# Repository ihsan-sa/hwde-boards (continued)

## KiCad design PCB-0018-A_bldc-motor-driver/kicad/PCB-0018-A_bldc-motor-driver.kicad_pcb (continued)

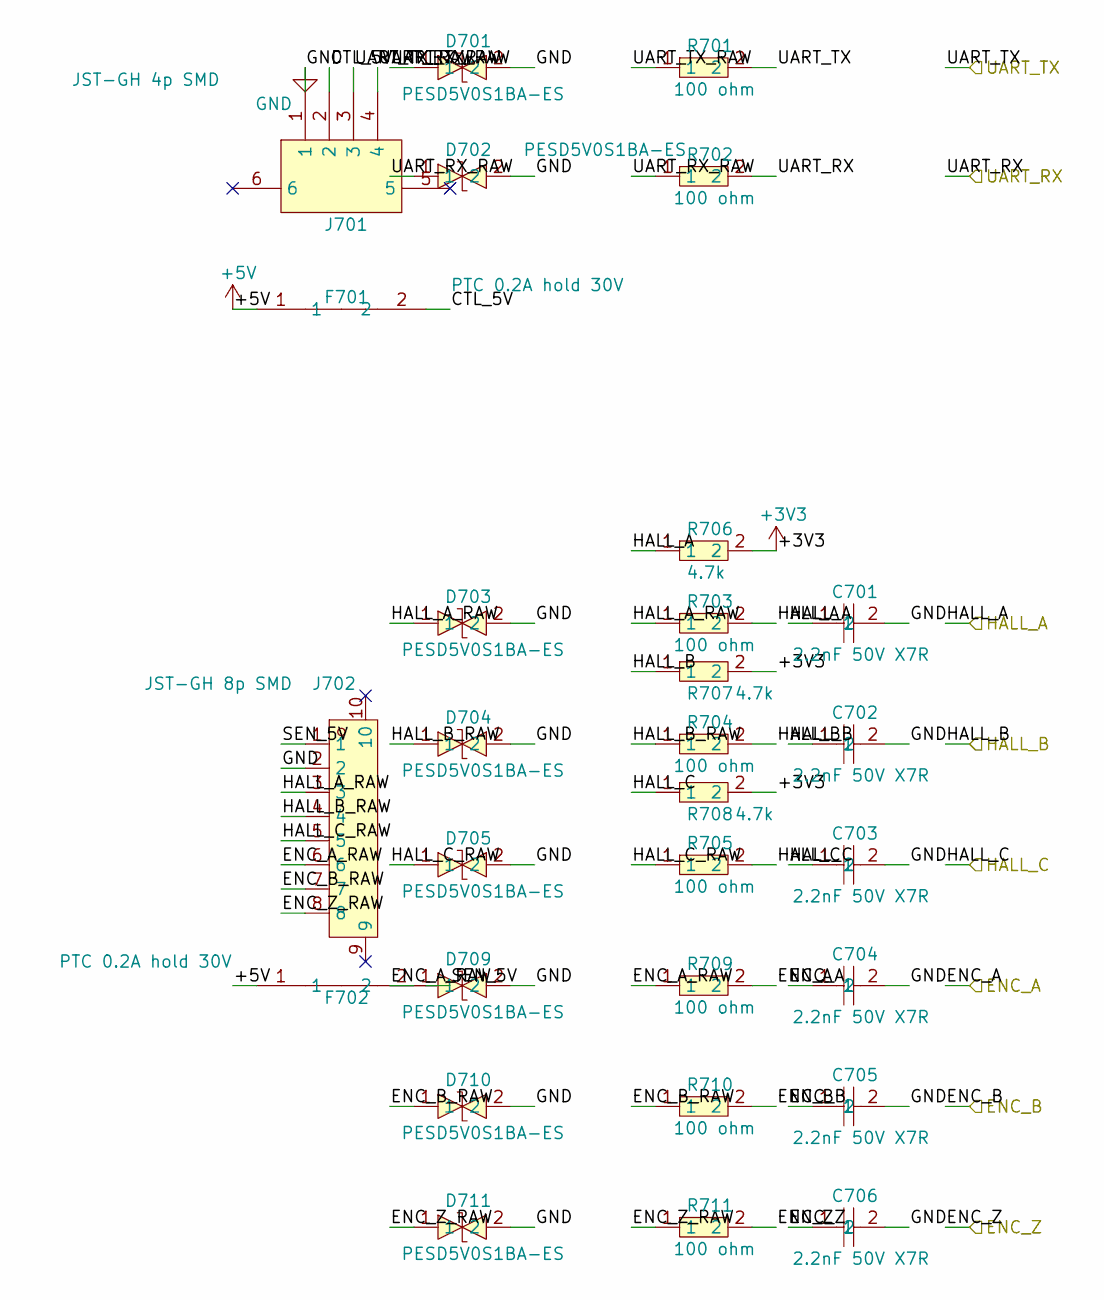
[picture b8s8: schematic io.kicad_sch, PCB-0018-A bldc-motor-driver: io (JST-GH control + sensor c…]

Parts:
C701, C702, C703, C704, C705, C706: 2.2nF 50V X7R; C0603; LCSC C1604
D701, D702, D703, D704, D705, D709, D710, D711: PESD5V0S1BA-ES; SOD-323_L1.7-W1.3-LS2.6-BI; LCSC C5180216
F701, F702: PTC 0.2A hold 30V; F1206; LCSC C69680
J701: JST-GH 4p SMD; CONN-SMD_4P-P1.25_SM04B-GHS-TB-LF-SN; LCSC C189895
J702: JST-GH 8p SMD; CONN-SMD_SH-SM08B-GHS-TB; LCSC C42376901
R701, R702, R703, R704, R705, R709, R710, R711: 100 ohm; R0603; LCSC C22775
R706, R707, R708: 4.7k; R0603; LCSC C23162

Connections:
+3V3: R706.2, R707.2, R708.2; also elsewhere on the board
+5V: F701.1, F702.1; also elsewhere on the board
/ENC_A: C704.1, R709.2; also elsewhere on the board
/ENC_B: C705.1, R710.2; also elsewhere on the board
/ENC_Z: C706.1, R711.2; also elsewhere on the board
/HALL_A: C701.1, R703.2, R706.1; also elsewhere on the board
/HALL_B: C702.1, R704.2, R707.1; also elsewhere on the board
/HALL_C: C703.1, R705.2, R708.1; also elsewhere on the board
/UART_RX: R702.2; also elsewhere on the board
/UART_TX: R701.2; also elsewhere on the board
/io/CTL_5V: F701.2, J701.2
/io/ENC_A_RAW: D709.1, J702.6, R709.1
/io/ENC_B_RAW: D710.1, J702.7, R710.1
/io/ENC_Z_RAW: D711.1, J702.8, R711.1
/io/HALL_A_RAW: D703.1, J702.3, R703.1
/io/HALL_B_RAW: D704.1, J702.4, R704.1
/io/HALL_C_RAW: D705.1, J702.5, R705.1
/io/SEN_5V: F702.2, J702.1
/io/UART_RX_RAW: D702.1, J701.4, R702.1
/io/UART_TX_RAW: D701.1, J701.3, R701.1
GND: C701.2, C702.2, C703.2, C704.2, C705.2, C706.2, D701.2, D702.2, D703.2, D704.2, D705.2, D709.2, D710.2, D711.2, J701.1, J702.2; also elsewhere on the board

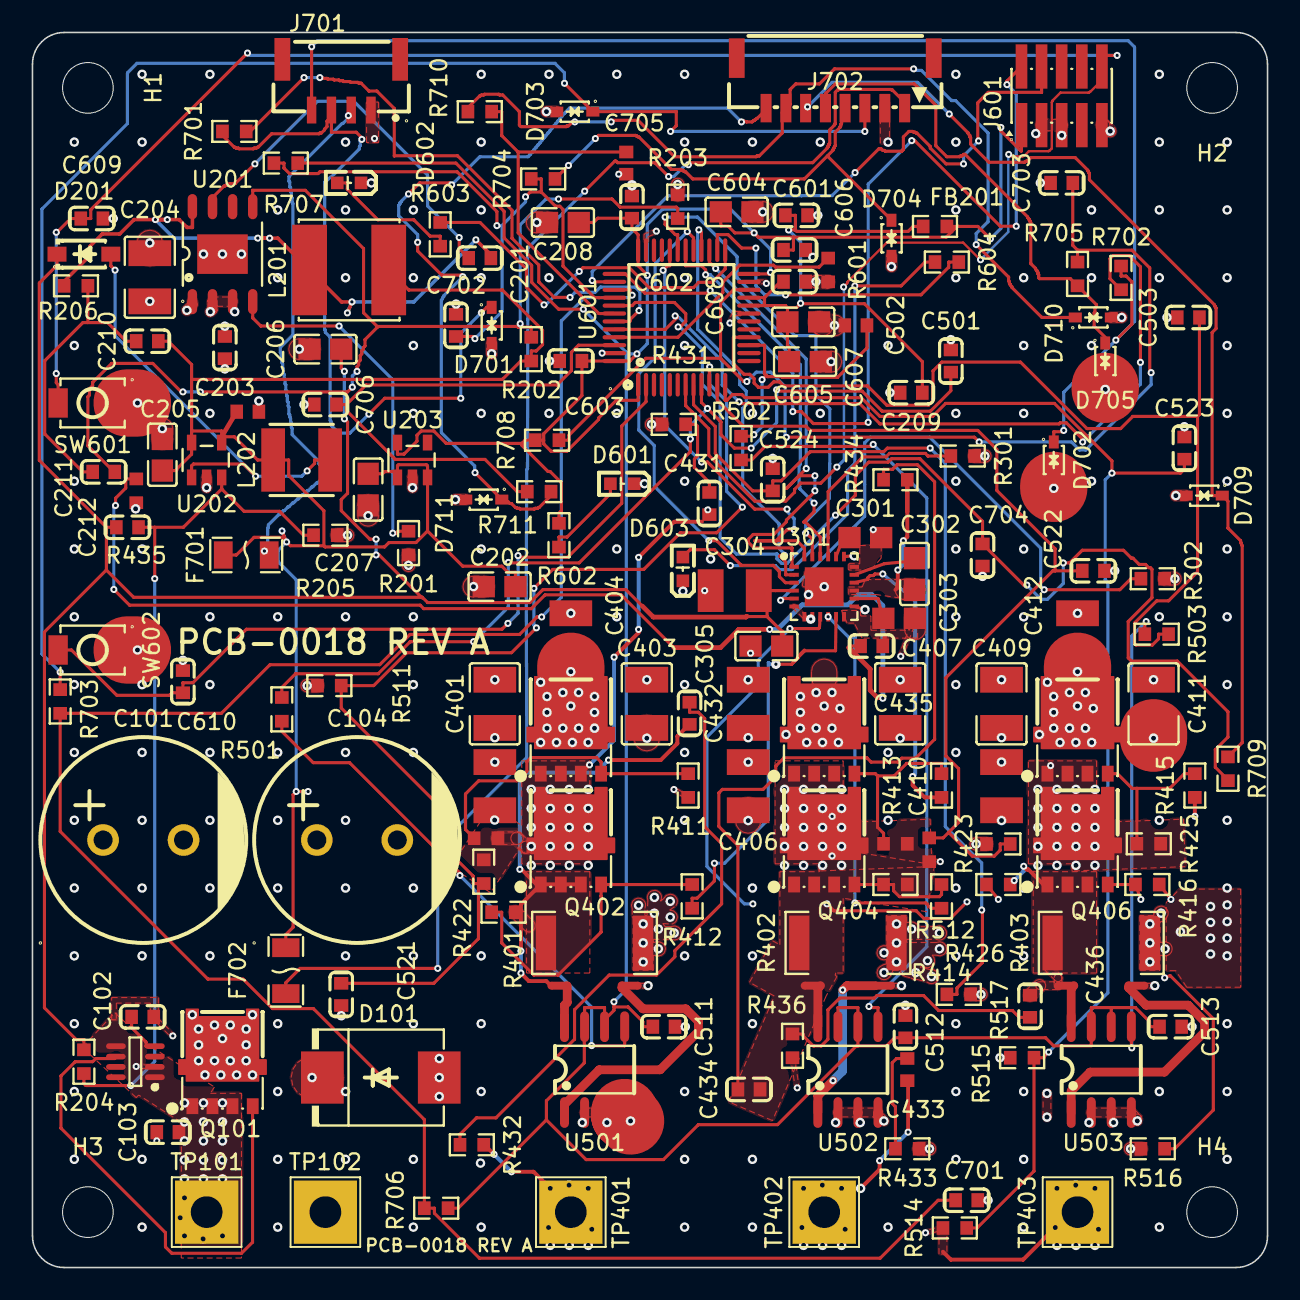
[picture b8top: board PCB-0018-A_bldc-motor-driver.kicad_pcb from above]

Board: 4 copper layers, 78.0 x 78.0 mm, 175 parts (1 on the bottom side), 95 nets.

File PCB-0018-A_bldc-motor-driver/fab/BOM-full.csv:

Comment,Designator,Qty Per Board,Footprint,MPN,LCSC,Assembly Class,Instructions
470uF 63V,"C101,C104",2,CAP-TH_BD13.0-P5.00-D1.2-FD,,C106675,smt_placed,
100nF 50V X7R,"C102,C103,C203,C209,C211,C213,C511,C512,C513,C524,C601,C602,C603,C608,C609,C610",16,C0603,,C14663,smt_placed,
2.2nF 50V X7R,"C201,C210,C501,C502,C503,C521,C522,C523,C701,C702,C703,C704,C705,C706",14,C0603,,C1604,smt_placed,
22uF 25V X5R,C202,1,C0805,,C45783,smt_placed,
10uF 50V X7R,"C204,C304,C401,C402,C403,C405,C406,C407,C409,C410,C411",11,C1210,,C2918502,smt_placed,
10uF 25V X5R,C205,1,C0805,,C15850,smt_placed,
1uF 50V X7R,"C206,C207,C208,C301,C302,C303,C305,C605,C607",9,C0805,,C28323,smt_placed,
1nF 50V X7R,C212,1,C0603,,C1588,smt_placed,
100nF 50V X7R,"C404,C408,C412",3,C1210,,C76567,smt_placed,
4.7uF 25V X5R,C604,1,C0805,,C1779,smt_placed,
10nF 50V X7R,C606,1,C0603,,C57112,smt_placed,
SMCJ28A,D101,1,SMC_L6.9-W5.8-LS7.9-RD,,C2943858,smt_placed,
MBR0520L,D201,1,SOD-123_L2.7-W1.6-LS3.7-RD-1,,C5563735,smt_placed,
LED green (power),D601,1,LED-SMD_L1.6-W0.8-R-RD,,C12624,smt_placed,
LED yellow (status),D602,1,LED-SMD_L1.6-W0.8-R-RD,,C2287,smt_placed,
LED red (fault),D603,1,LED-SMD_L1.6-W0.8-R-RD,,C2286,smt_placed,
PESD5V0S1BA-ES,"D701,D702,D703,D704,D705,D709,D710,D711",8,SOD-323_L1.7-W1.3-LS2.6-BI,,C5180216,smt_placed,
PTC 0.2A hold 30V,"F701,F702",2,F1206,,C69680,smt_placed,
600ohm@100MHz ferrite,FB201,1,R0603,,C1002,smt_placed,
SWD 2x5 1.27mm,J601,1,CONN-SMD_10P-P1.27_XFCN_PZ127VS-12-10-H10-A38,,C2935458,smt_placed,
JST-GH 4p SMD,J701,1,CONN-SMD_4P-P1.25_SM04B-GHS-TB-LF-SN,,C189895,smt_placed,
JST-GH 8p SMD,J702,1,CONN-SMD_SH-SM08B-GHS-TB,,C42376901,smt_placed,
22uH shielded,L201,1,IND-SMD_L6.0-W6.0,,C2849539,smt_placed,
22uH shielded,L202,1,IND-SMD_L4.0-W4.0_LQH44PN2R2MP0L,,C135264,smt_placed,
NTMFS5C628NL,"Q101,Q401,Q402,Q403,Q404,Q405,Q406",7,DFN-5_L4.9-W5.9-P1.27-LS6.2-BL,,C145537,smt_placed,
31.6k 1%,R201,1,R0603,,C25967,smt_placed,
33.2k 1%,R202,1,R0603,,C23003,smt_placed,
10k,"R203,R205,R302,R421,R422,R423,R424,R425,R426,R511,R513,R515,R517",13,R0603,,C25804,smt_placed,
86.6k 1%,R204,1,R0603,,C23121,smt_placed,
100k,R206,1,R0603,,C25803,smt_placed,
40.2k 1%,R301,1,R0603,,C12447,smt_placed,
3mR 2512 3W 1%,"R401,R402,R403",3,R2512,,C5375459,smt_placed,
10R,"R411,R412,R413,R414,R415,R416",6,R0603,,C22859,smt_placed,
100 ohm,"R501,R502,R503,R701,R702,R703,R704,R705,R709,R710,R711",11,R0603,,C22775,smt_placed,
150k,"R510,R512,R514,R516",4,R0603,,C22807,smt_placed,
10k 1%,R601,1,R0603,,C25804,smt_placed,
1k 1%,"R602,R603,R604",3,R0603,,C21190,smt_placed,
4.7k,"R706,R707,R708",3,R0603,,C23162,smt_placed,
Reset switch SMD,SW601,1,SW-SMD_L3.9-W3.0-P4.45,,C720477,smt_placed,
User switch SMD,SW602,1,SW-SMD_L3.9-W3.0-P4.45,,C720477,smt_placed,
LM74500-Q1,U101,1,SOT-23-8_L3.0-W1.7-P0.65-LS2.8-BR,,C5219210,smt_placed,
LM5164,U201,1,SO-8_L4.9-W3.9-P1.27-LS6.0-BL-EP,,C477928,smt_placed,
TPS61040,U202,1,SOT-23-5_L2.9-W1.6-P0.95-LS2.8-BL,,C7722,smt_placed,
TLV75733,U203,1,SOT-23-5_L2.9-W1.6-P0.95-LS2.8-BL,,C485517,smt_placed,
DRV8300DRGER,U301,1,VQFN-24_L4.0-W4.0-P0.50-TL-EP2.5,,C3655801,smt_placed,
INA240A1,"U501,U502,U503",3,SOIC-8_L5.0-W4.0-P1.27-LS6.0-BL,,C2060769,smt_placed,
STM32G431CBT6,U601,1,LQFP-48_L7.0-W7.0-P0.50-LS9.0-BL,,C529355,smt_placed,
2.2nF 100V DNP,"C431,C432,C433,C434,C435,C436",6,C0603,,,dnp,DO NOT POPULATE - this land ships empty.
3.3R DNP,"R431,R432,R433,R434,R435,R436",6,R0603,,,dnp,DO NOT POPULATE - this land ships empty.
,"H1,H2,H3,H4,NT401,NT402,NT403,NT404,NT405,NT406,TP101,TP102,TP401,TP402,TP403",15,,,,board_feature,Realised in copper - nothing to buy or place.

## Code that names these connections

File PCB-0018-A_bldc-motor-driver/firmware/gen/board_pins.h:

/* board_pins.h - GENERATED by /fwe pinmap.py from PCB-0018-A_bldc-motor-driver/kicad/PCB-0018-A_bldc-motor-driver.net.
 * Do not edit: regenerate with pinmap.py --workspace <board>; the build runs pinmap.py --check.
 * netlist sha256 31d0f8db9afdf43fd3d7fb257b848f2352fb8ab753055de13cf5ccaa2cdd9446 */
#ifndef BOARD_PINS_H
#define BOARD_PINS_H

#define BOARD_ID "PCB-0018-A"
#define BOARD_MCU "STM32G431CBT6"

/* PC13 (pin 2) button */
#define PIN_USER_SW_PORT GPIOC
#define PIN_USER_SW_PIN 13u

/* PG10 (pin 7) reset */
#define PIN_NRST_PORT GPIOG
#define PIN_NRST_PIN 10u

/* PA0 (pin 8) v_bus */
#define PIN_VBUS_SENSE_PORT GPIOA
#define PIN_VBUS_SENSE_PIN 0u
#define PIN_VBUS_SENSE_ADC 1u
#define PIN_VBUS_SENSE_ADC_CH 1u /* ADC12_IN1 */
#define PIN_VBUS_SENSE_COMP 3u /* COMP3_INP */

/* PA1 (pin 9) i_sense */
#define PIN_ISENSE_A_PORT GPIOA
#define PIN_ISENSE_A_PIN 1u
#define PIN_ISENSE_A_ADC 1u
#define PIN_ISENSE_A_ADC_CH 2u /* ADC12_IN2 */
#define PIN_ISENSE_A_COMP 1u /* COMP1_INP */

/* PA2 (pin 10) v_phase */
#define PIN_VSENSE_A_PORT GPIOA
#define PIN_VSENSE_A_PIN 2u
#define PIN_VSENSE_A_ADC 1u
#define PIN_VSENSE_A_ADC_CH 3u /* ADC1_IN3 */

/* PA3 (pin 11) v_phase */
#define PIN_VSENSE_B_PORT GPIOA
#define PIN_VSENSE_B_PIN 3u
#define PIN_VSENSE_B_ADC 1u
#define PIN_VSENSE_B_ADC_CH 4u /* ADC1_IN4 */
#define PIN_VSENSE_B_COMP 2u /* COMP2_INP */

/* PA4 (pin 12) v_phase */
#define PIN_VSENSE_C_PORT GPIOA
#define PIN_VSENSE_C_PIN 4u
#define PIN_VSENSE_C_ADC 2u
#define PIN_VSENSE_C_ADC_CH 17u /* ADC2_IN17 */

/* PA7 (pin 15) i_sense */
#define PIN_ISENSE_B_PORT GPIOA
#define PIN_ISENSE_B_PIN 7u
#define PIN_ISENSE_B_ADC 2u
#define PIN_ISENSE_B_ADC_CH 4u /* ADC2_IN4 */
#define PIN_ISENSE_B_COMP 2u /* COMP2_INP */

/* PB0 (pin 16) i_sense */
#define PIN_ISENSE_C_PORT GPIOB
#define PIN_ISENSE_C_PIN 0u
#define PIN_ISENSE_C_ADC 1u
#define PIN_ISENSE_C_ADC_CH 15u /* ADC1_IN15 */
#define PIN_ISENSE_C_COMP 4u /* COMP4_INP */

/* PB10 (pin 22) hall */
#define PIN_HALL_C_PORT GPIOB
#define PIN_HALL_C_PIN 10u
#define PIN_HALL_C_AF 1u /* TIM2_CH3 */

/* PB11 (pin 25) led */
#define PIN_LED_STATUS_PORT GPIOB
#define PIN_LED_STATUS_PIN 11u

/* PB12 (pin 26) led */
#define PIN_LED_FAULT_PORT GPIOB
#define PIN_LED_FAULT_PIN 12u

/* PB13 (pin 27) gate_lo */
#define PIN_INLA_PORT GPIOB
#define PIN_INLA_PIN 13u
#define PIN_INLA_AF 6u /* TIM1_CH1N */

/* PB14 (pin 28) gate_lo */
#define PIN_INLB_PORT GPIOB
#define PIN_INLB_PIN 14u
#define PIN_INLB_AF 6u /* TIM1_CH2N */

/* PB15 (pin 29) gate_lo */
#define PIN_INLC_PORT GPIOB
#define PIN_INLC_PIN 15u
#define PIN_INLC_AF 4u /* TIM1_CH3N */

/* PA8 (pin 30) gate_hi */
#define PIN_INHA_PORT GPIOA
#define PIN_INHA_PIN 8u
#define PIN_INHA_AF 6u /* TIM1_CH1 */

/* PA9 (pin 31) gate_hi */
#define PIN_INHB_PORT GPIOA
#define PIN_INHB_PIN 9u
#define PIN_INHB_AF 6u /* TIM1_CH2 */

/* PA10 (pin 32) gate_hi */
#define PIN_INHC_PORT GPIOA
#define PIN_INHC_PIN 10u
#define PIN_INHC_AF 6u /* TIM1_CH3 */

/* PA13 (pin 37) swd */
#define PIN_SWDIO_PORT GPIOA
#define PIN_SWDIO_PIN 13u

/* PA14 (pin 38) swd */
#define PIN_SWCLK_PORT GPIOA
#define PIN_SWCLK_PIN 14u

/* PA15 (pin 39) hall */
#define PIN_HALL_A_PORT GPIOA
#define PIN_HALL_A_PIN 15u
#define PIN_HALL_A_AF 1u /* TIM2_CH1 */

/* PB3 (pin 40) hall */
#define PIN_HALL_B_PORT GPIOB
#define PIN_HALL_B_PIN 3u
#define PIN_HALL_B_AF 1u /* TIM2_CH2 */

/* PB4 (pin 41) encoder */
#define PIN_ENC_A_PORT GPIOB
#define PIN_ENC_A_PIN 4u
#define PIN_ENC_A_AF 2u /* TIM3_CH1 */

/* PB5 (pin 42) encoder */
#define PIN_ENC_B_PORT GPIOB
#define PIN_ENC_B_PIN 5u
#define PIN_ENC_B_AF 2u /* TIM3_CH2 */

/* PB6 (pin 43) uart_tx */
#define PIN_UART_TX_PORT GPIOB
#define PIN_UART_TX_PIN 6u
#define PIN_UART_TX_AF 7u /* USART1_TX */

/* PB7 (pin 44) uart_rx */
#define PIN_UART_RX_PORT GPIOB
#define PIN_UART_RX_PIN 7u
#define PIN_UART_RX_AF 7u /* USART1_RX */

/* PB8 (pin 45) boot */
#define PIN_BOOT0_PORT GPIOB
#define PIN_BOOT0_PIN 8u

/* PB9 (pin 46) encoder_index */
#define PIN_ENC_Z_PORT GPIOB
#define PIN_ENC_Z_PIN 9u

/* unused: PC14 PC15 PF0 PF1 PA5 PA6 PB1 PB2 PA11 PA12 */
#define RAIL__3V3_V 3.3f
#define RAIL_VDDA_V 3.3f

#define VBUS_SENSE_RATIO 16.0f /* VM: 150000/10000 ohm */
#define ISENSE_A_GAIN 20.0f /* U501 INA240A1 */
#define ISENSE_A_REF_V 1.65f
#define ISENSE_A_SHUNT_OHM 0.003f /* R401 */
#define VSENSE_A_RATIO 16.0f /* PHASE_A: 150000/10000 ohm */
#define VSENSE_B_RATIO 16.0f /* PHASE_B: 150000/10000 ohm */
#define VSENSE_C_RATIO 16.0f /* PHASE_C: 150000/10000 ohm */
#define ISENSE_B_GAIN 20.0f /* U502 INA240A1 */
#define ISENSE_B_REF_V 1.65f
#define ISENSE_B_SHUNT_OHM 0.003f /* R402 */
#define ISENSE_C_GAIN 20.0f /* U503 INA240A1 */
#define ISENSE_C_REF_V 1.65f
#define ISENSE_C_SHUNT_OHM 0.003f /* R403 */

#endif /* BOARD_PINS_H */

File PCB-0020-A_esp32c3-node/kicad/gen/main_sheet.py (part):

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SOURCE for kicad/main.kicad_sch (build output). Refdes ranges
(architecture/sheets.md): U1, U5-U9, J3-J9, D10-D19, R10-R19, C10-C19,
SW1-SW9; pwr_base=200. +3V3 / GND / VBUS / VBAT are global power symbols.
Cross-sheet signals arrive as hierarchical pins USB_DP, USB_DM, VBAT_SENSE.

Pin ground truth (schlib --pins + parts/C2838502.json, DS Table 3-1):
  U1 1,2,11,14,36-53 GND (49 = EPAD); 3 3V3; 8 EN; 5 IO2; 6 IO3; 12 IO0;
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    # ---- status LED on IO10 (not a strap) ---------------------------------
    sh.add_component("aiee:0603WAF1001T5E", "R16", "1k",
                     at=(101.60, 203.20), footprint=f"{FP}:R0603")
    sh.wire_pins("R16", {"1": "LED", "2": "LED_A"})
    sh.add_component("aiee:0805G", "D10", "Green LED (status)",
                     at=(127.00, 203.20), footprint=f"{FP}:LED0805-R-RD",
                     expect={"1": "A", "2": "K"})
    sh.wire_pins("D10", {"1": "LED_A", "2": "GND"})

    # ---- U5 BME280 (I2C, 0x76) --------------------------------------------
    sh.place_ic_with_decoupling(
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    sh.wire_pins("J5", {"1": "VBUS", "2": "VBAT", "3": "+3V3", "4": "GND"})

    # ---- cross-sheet signals --------------------------------------------
    sh.hier_pin("USB_DP", shape="bidirectional", at=(101.60, 254.00))
    sh.hier_pin("USB_DM", shape="bidirectional", at=(101.60, 266.70))
    sh.hier_pin("VBAT_SENSE", shape="input", at=(101.60, 279.40))

    # ---- rails (flags live on the power sheet) ----------------------------
    sh.power_flag("+3V3", at=(165.10, 254.00), sym="power:+3V3", flag=False)
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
